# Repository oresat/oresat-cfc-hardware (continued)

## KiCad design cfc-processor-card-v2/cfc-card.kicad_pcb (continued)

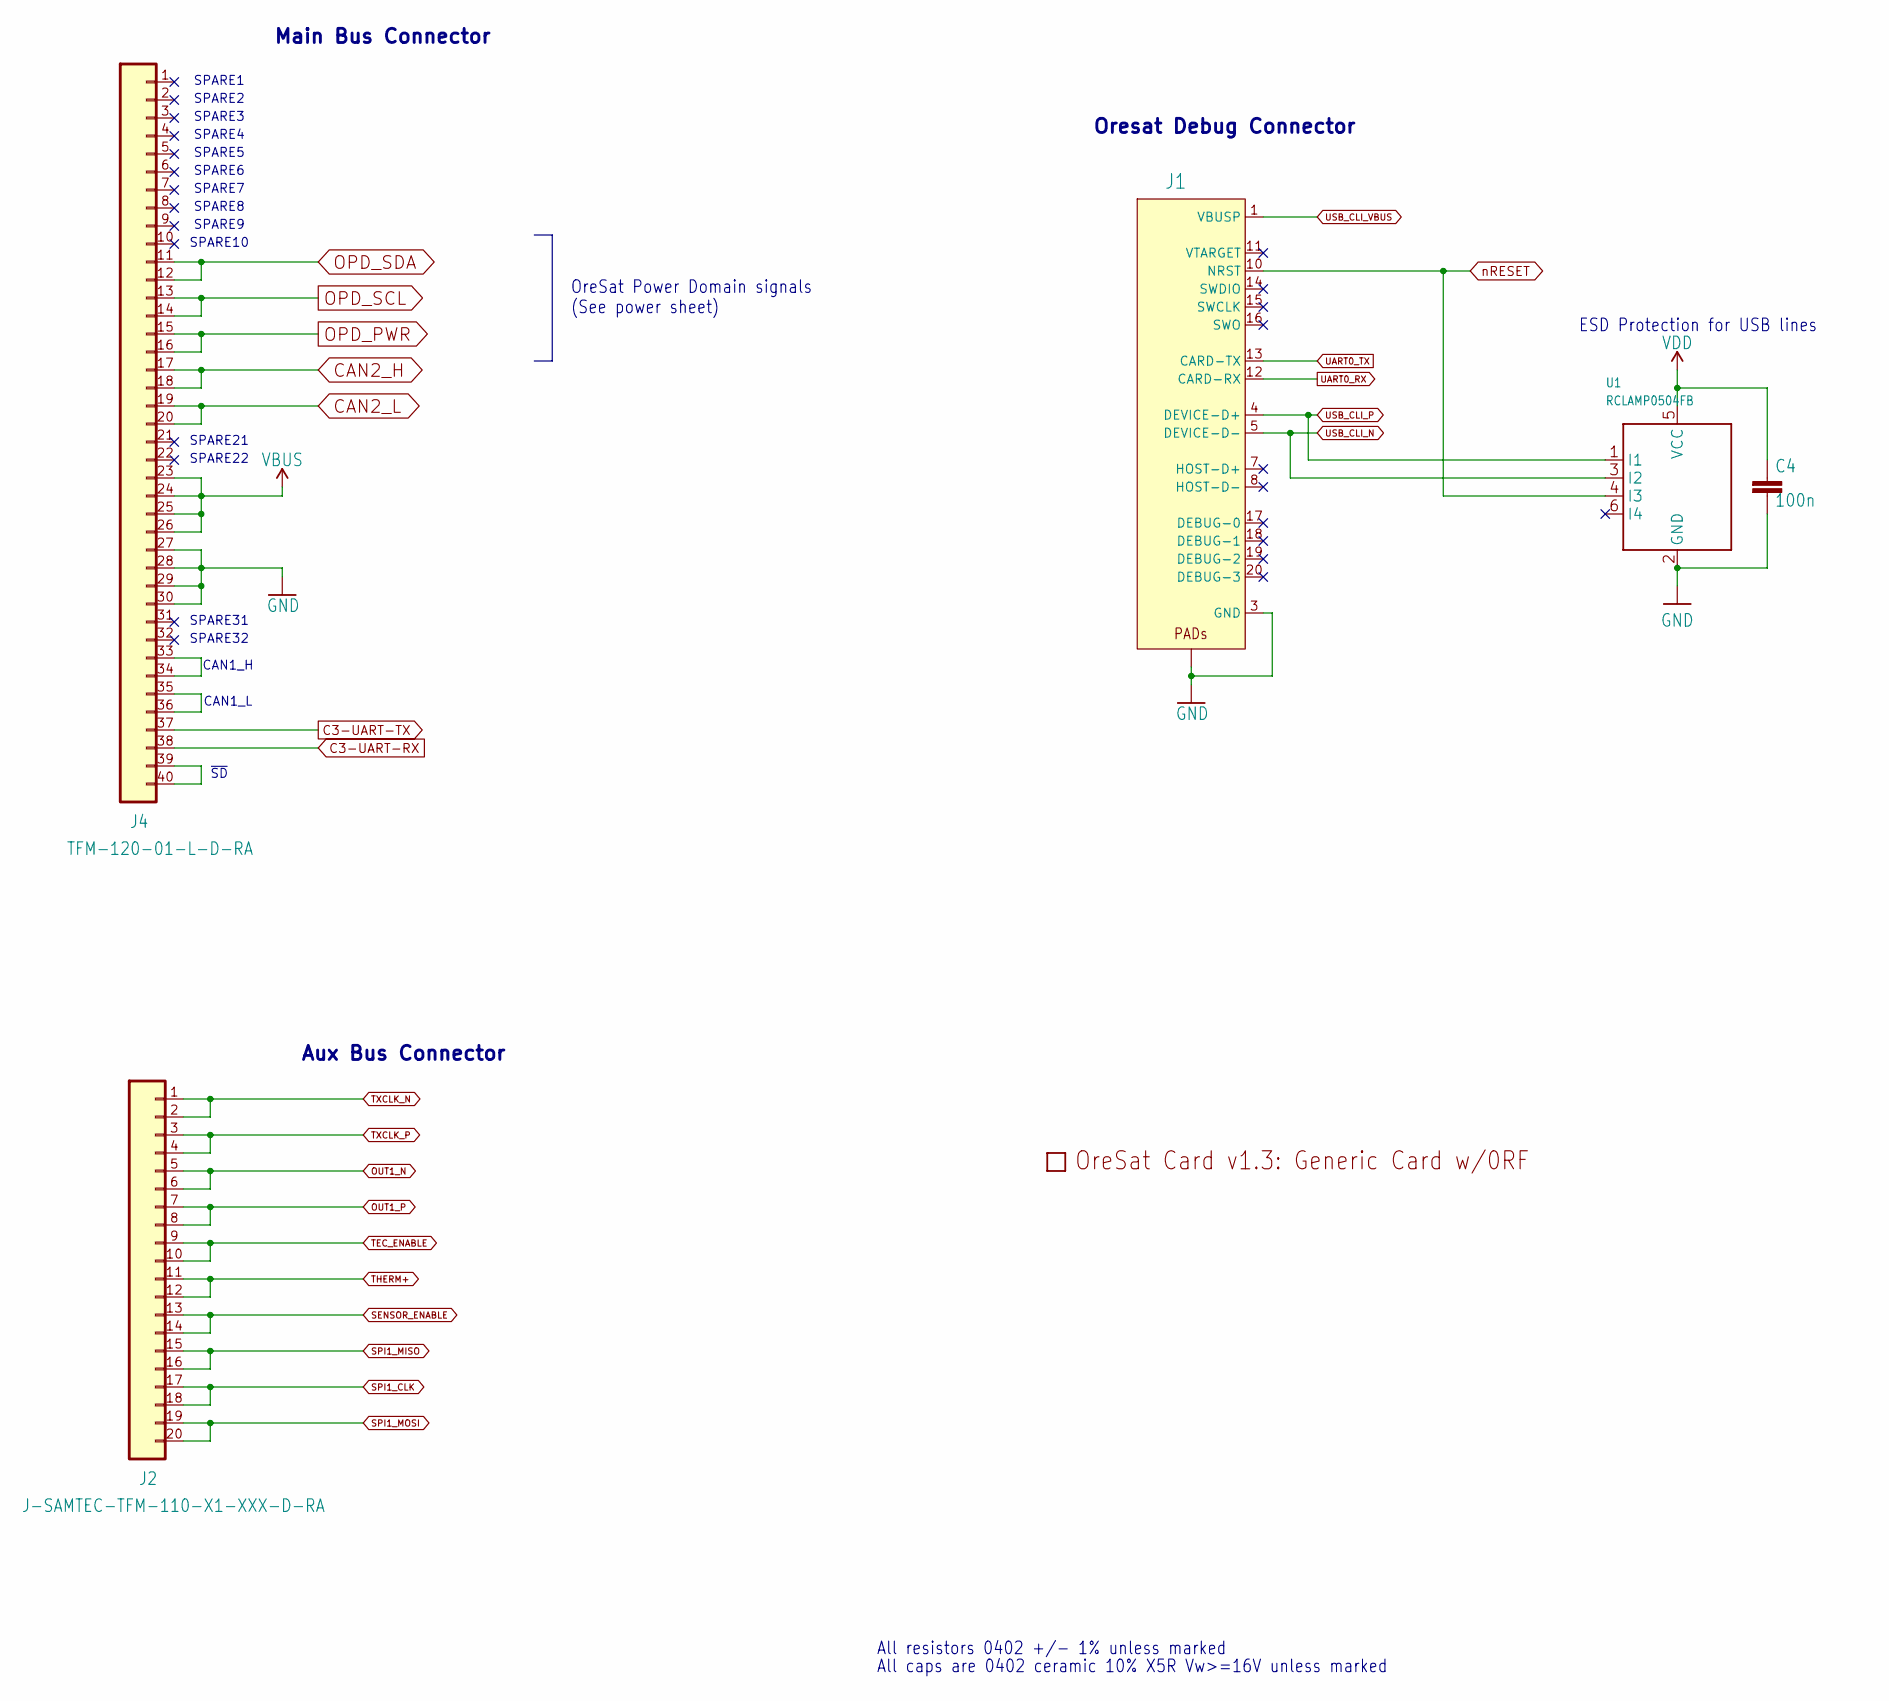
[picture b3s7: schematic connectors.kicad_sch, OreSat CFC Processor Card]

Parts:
C4: 100n; 0603-C-NOSILK; MPN TMK107BJ104KAHT
J1: 2-1734592-0; J-TE-2-1734592-0; MPN 2-1734592-0
J2: J-SAMTEC-TFM-110-X1-XXX-D-RA; MPN TFM-110-01-L-D-RA
J4: TFM-120-01-L-D-RA; J-SAMTEC-TFM-120-X1-XXX-D-RA; MPN TFM-120-01-L-D-RA
PCB1: ORESAT-CARD-V1.3-GENERIC-0RF; MPN N/A
U1: RCLAMP0504FB; SC70-6; MPN RCLAMP0504FBTCT

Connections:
C3-UART-RX: J4.38; also elsewhere on the board
C3-UART-TX: J4.37; also elsewhere on the board
CAN2_H: J4.17, J4.18; also elsewhere on the board
CAN2_L: J4.19, J4.20; also elsewhere on the board
GND: C4.2, J1.3 (GND), J1.6 (GND), J1.9 (GND), J1.PAD1 (PAD), J1.PAD2 (PAD), J4.27, J4.28, J4.29, J4.30, U1.2 (GND); also elsewhere on the board
unnamed: J4.33, J4.34
unnamed: J4.35, J4.36
unnamed: J4.39, J4.40
OPD_PWR: J4.15, J4.16; also elsewhere on the board
OPD_SCL: J4.13, J4.14; also elsewhere on the board
OPD_SDA: J4.11, J4.12; also elsewhere on the board
OUT1_N: J2.5, J2.6; also elsewhere on the board
OUT1_P: J2.7, J2.8; also elsewhere on the board
SENSOR_ENABLE: J2.13, J2.14; also elsewhere on the board
SPI1_CLK: J2.17, J2.18; also elsewhere on the board
SPI1_MISO: J2.15, J2.16; also elsewhere on the board
SPI1_MOSI: J2.19, J2.20; also elsewhere on the board
TEC_ENABLE: J2.9, J2.10; also elsewhere on the board
THERM+: J2.11, J2.12; also elsewhere on the board
TXCLK_N: J2.1, J2.2; also elsewhere on the board
TXCLK_P: J2.3, J2.4; also elsewhere on the board
UART0_RX: J1.12 (CARD-RX); also elsewhere on the board
UART0_TX: J1.13 (CARD-TX); also elsewhere on the board
USB_CLI_N: J1.5 (DEVICE-D-), U1.3 (I2); also elsewhere on the board
USB_CLI_P: J1.4 (DEVICE-D+), U1.1 (I1); also elsewhere on the board
USB_CLI_VBUS: J1.1 (VBUSP), J1.2 (VBUSP); also elsewhere on the board
VBUS: J4.23, J4.24, J4.25, J4.26; also elsewhere on the board
VDD: C4.1, U1.5 (VCC); also elsewhere on the board
nRESET: J1.10 (NRST), U1.4 (I3); also elsewhere on the board

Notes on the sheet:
SPARE31
Oresat Debug Connector
All caps are 0402 ceramic 10% X5R Vw>=16V unless marked
SPARE10
ESD Protection for USB lines
~{SD}
All resistors 0402 +/- 1% unless marked
SPARE8
CAN1_L
SPARE3
SPARE32
SPARE5
SPARE2
SPARE22
OreSat Power Domain signals (See power sheet)
Main Bus Connector
SPARE21
SPARE6
CAN1_H
SPARE7
Aux Bus Connector
SPARE4
SPARE9
SPARE1

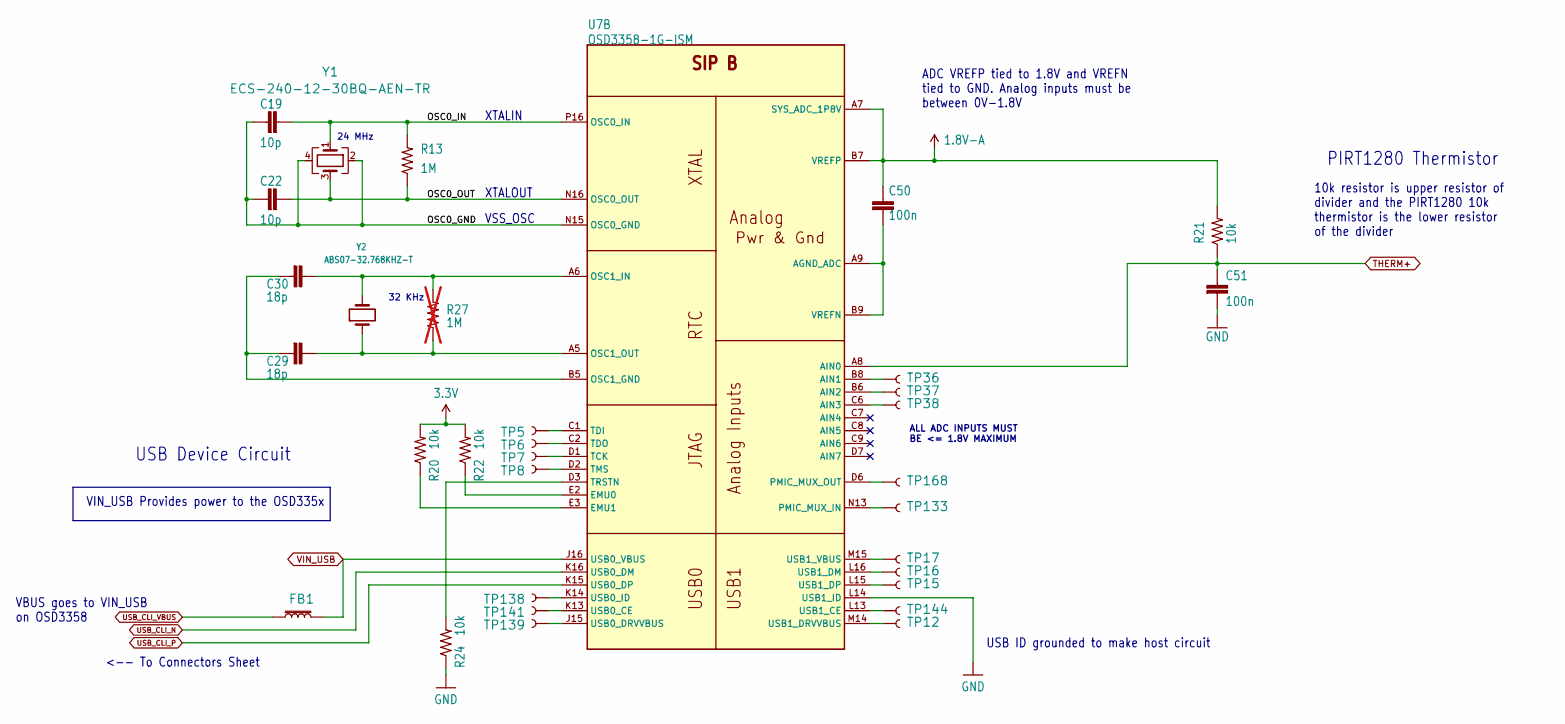
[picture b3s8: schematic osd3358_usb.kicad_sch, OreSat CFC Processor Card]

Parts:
C19, C22: 10p; 0603-C-NOSILK; MPN C0603C100J5GACAUTO
C29, C30: 18p; 0603-C-NOSILK; MPN C0603C180F5GACAUTO
C50, C51: 100n; 0603-C-NOSILK; MPN TMK107BJ104KAHT
FB1: BLM18KG300JH1D; L_0603_1608Metric; MPN BLM18KG300JH1D
R13: 1M; 0603-C-NOSILK; MPN RMCF0603FG1M00
R20, R21, R22, R24: 10k; 0603-C-NOSILK; MPN RMCF0603FT10K0
R27: 1M; 0603-C-NOSILK; not fitted
TP5, TP6, TP7, TP8, TP12, TP15, TP16, TP17, TP36, TP37, TP38, TP133, TP138, TP139, TP141, TP144, TP168: TEST-POINT3X4; PAD.03X.04
U7: OSD3358-1G-ISM; U-Octavo-OSD335X-BGA-256; MPN OSD3358-1G-ISM
Y1: ECS-240-12-30BQ-AEN-TR; CRYSTAL-5X3.2-4SMD; MPN ECS-240-12-30BQ-AEN-TR
Y2: ABS07-32.768KHZ-T; CRYSTAL_3.2X1.5; MPN ABS07-32.768KHZ-T

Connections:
1.8V-A: C50.1, R21.2, U7.A7 (SYS_ADC_1P8V), U7.B7 (VREFP)
3.3V: R20.2, R22.2; also elsewhere on the board
/OSD3358: SIP B (USB, XTAL, ADC)/OSC0_GND: C19.1, C22.1, U7.N15 (OSC0_GND), Y1.2, Y1.4
/OSD3358: SIP B (USB, XTAL, ADC)/OSC0_IN: C19.2, R13.2, U7.P16 (OSC0_IN), Y1.1
/OSD3358: SIP B (USB, XTAL, ADC)/OSC0_OUT: C22.2, R13.1, U7.N16 (OSC0_OUT), Y1.3
GND: C51.2, R24.1, U7.L14 (USB1_ID); also elsewhere on the board
unnamed: TP5.P$1 (1), U7.C1 (TDI)
unnamed: TP6.P$1 (1), U7.C2 (TDO)
unnamed: TP7.P$1 (1), U7.D1 (TCK)
unnamed: TP8.P$1 (1), U7.D2 (TMS)
unnamed: TP12.P$1 (1), U7.M14 (USB1_DRVVBUS)
unnamed: TP15.P$1 (1), U7.L15 (USB1_DP)
unnamed: TP16.P$1 (1), U7.L16 (USB1_DM)
unnamed: TP17.P$1 (1), U7.M15 (USB1_VBUS)
unnamed: TP36.P$1 (1), U7.B8 (AIN1)
unnamed: TP37.P$1 (1), U7.B6 (AIN2)
unnamed: TP38.P$1 (1), U7.C6 (AIN3)
unnamed: TP133.P$1 (1), U7.N13 (PMIC_MUX_IN)
unnamed: TP138.P$1 (1), U7.K14 (USB0_ID)
unnamed: TP139.P$1 (1), U7.J15 (USB0_DRVVBUS)
unnamed: TP141.P$1 (1), U7.K13 (USB0_CE)
unnamed: TP144.P$1 (1), U7.L13 (USB1_CE)
unnamed: TP168.P$1 (1), U7.D6 (PMIC_MUX_OUT)
unnamed: C50.2, U7.A9 (AGND_ADC), U7.B9 (VREFN)
unnamed: R22.1, U7.E2 (EMU0)
unnamed: R20.1, U7.E3 (EMU1)
unnamed: C29.2, C30.2, U7.B5 (OSC1_GND)
unnamed: C30.1, R27.2, U7.A6 (OSC1_IN), Y2.2
unnamed: C29.1, R27.1, U7.A5 (OSC1_OUT), Y2.1
unnamed: R24.2, U7.D3 (TRSTN)
THERM+: C51.1, R21.1, U7.A8 (AIN0); also elsewhere on the board
USB_CLI_N: U7.K16 (USB0_DM); also elsewhere on the board
USB_CLI_P: U7.K15 (USB0_DP); also elsewhere on the board
USB_CLI_VBUS: FB1.1; also elsewhere on the board
VIN_USB: FB1.2, U7.J16 (USB0_VBUS); also elsewhere on the board

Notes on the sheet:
XTALOUT
<-- To Connectors Sheet
USB ID grounded to make host circuit
VSS_OSC
ADC VREFP tied to 1.8V and VREFN tied to GND. Analog inputs must be between 0V-1.8V
PIRT1280 Thermistor
VBUS goes to VIN_USB on OSD3358
USB Device Circuit
VIN_USB Provides power to the OSD335x
24 MHz
10k resistor is upper resistor of divider and the PIRT1280 10k thermistor is the lower resistor of the divider
ALL ADC INPUTS MUST BE <= 1.8V MAXIMUM
32 KHz
XTALIN

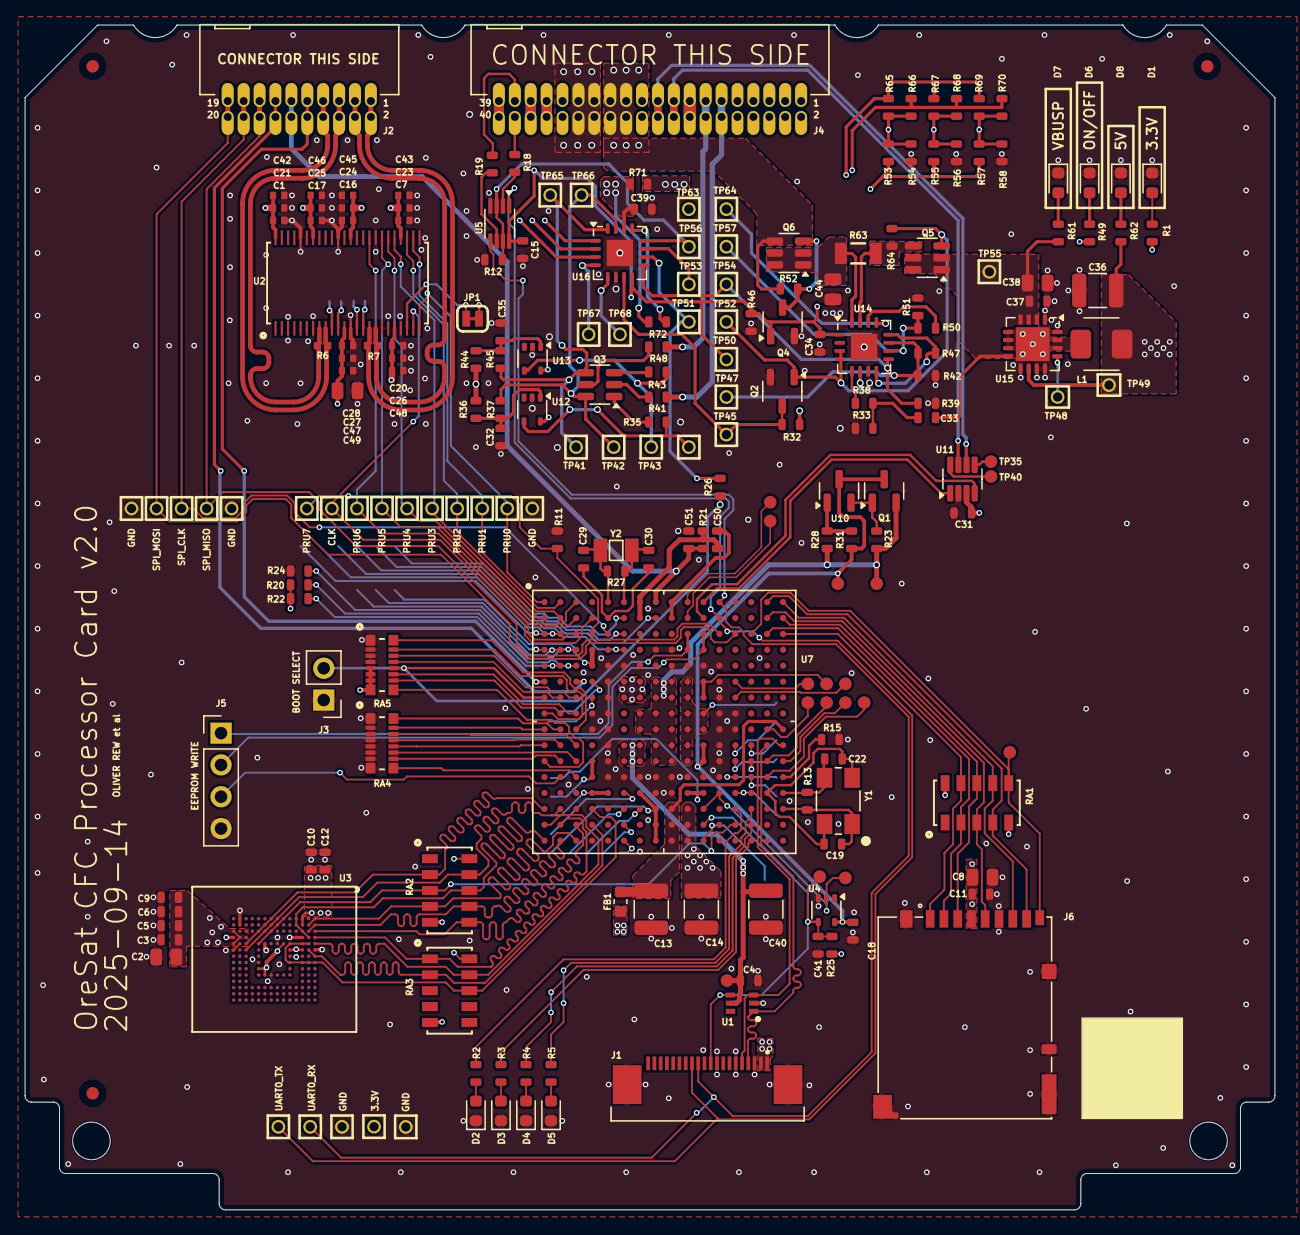
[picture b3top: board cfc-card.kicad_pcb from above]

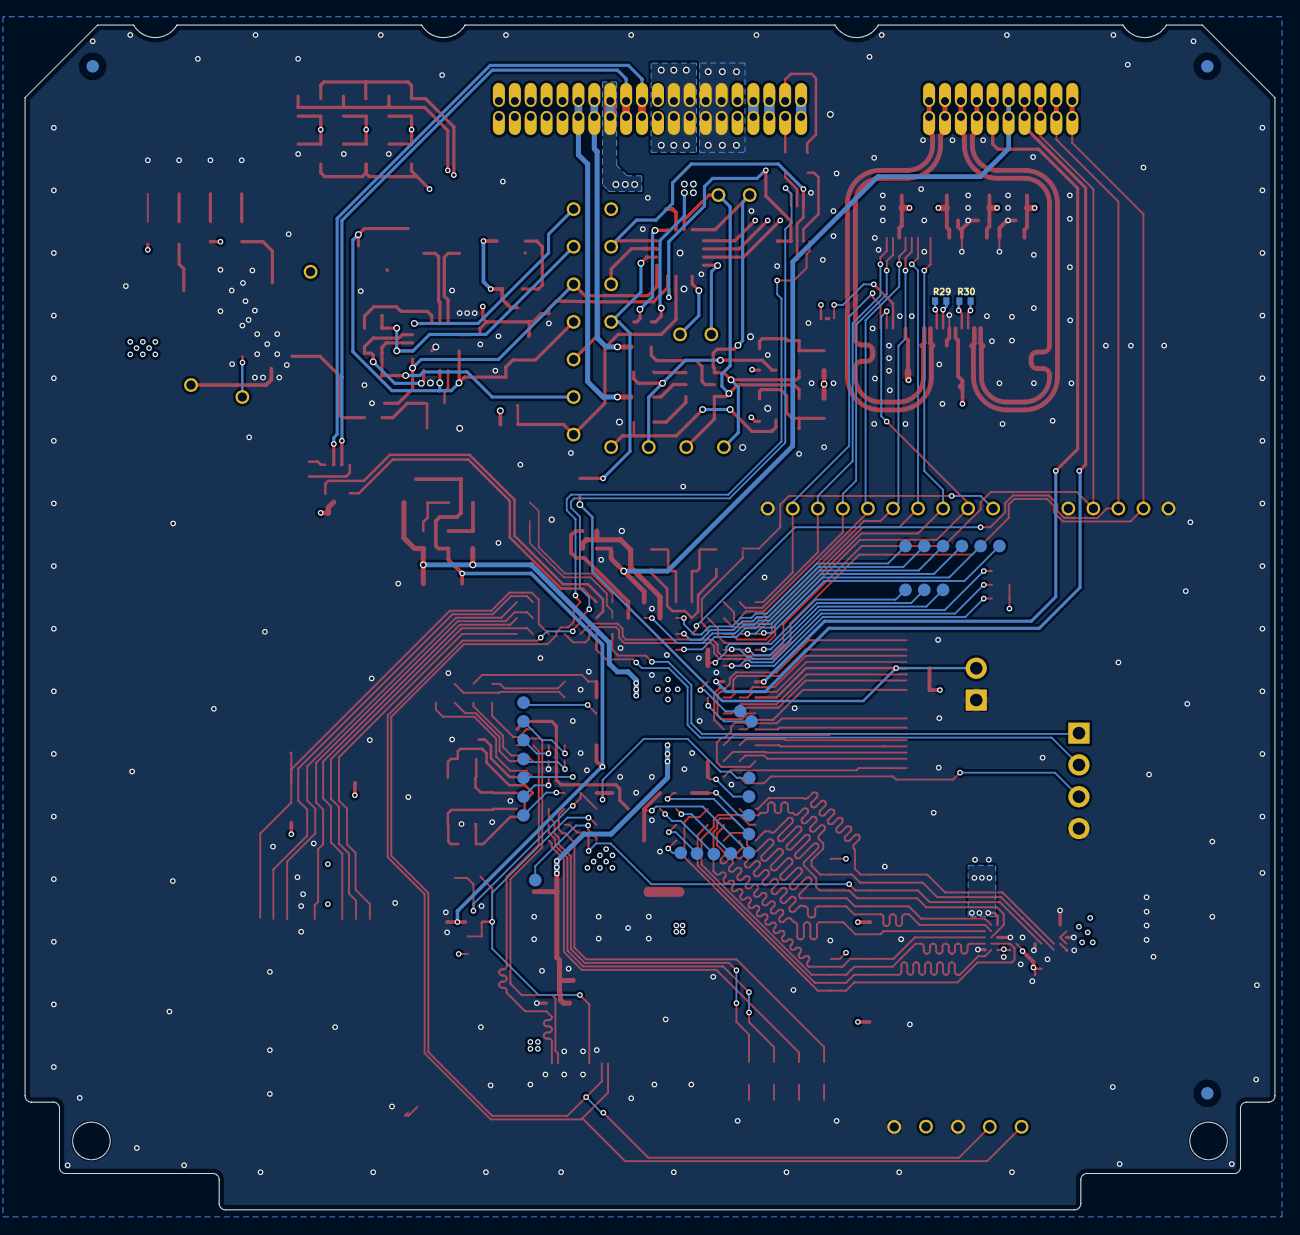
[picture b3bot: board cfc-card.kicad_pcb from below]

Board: 4 copper layers, 99.8 x 94.6 mm, 250 parts (33 on the bottom side), 193 nets.

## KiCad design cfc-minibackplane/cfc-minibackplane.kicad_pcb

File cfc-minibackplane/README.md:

# Oresat CFC Mini-Backplane

This is the backplane for UMBC's Air Harp 2 sensor, which is going to include a PIRT SWIR sensor using OreSat's CFC system.

## Requirements:

* Match the DXF outline from Joe, including placement of connectors and the fastener holes.
   * Probably remove solder mask from both sides of those fastener holes just in case.
   * Probably put the external connectors in the upper right hand corner.
* Use an OreSat 20 pin debug connector on this backplane so we can run USB from the CFC processor to the external connector using the CFC processor's debug connector.
* External connections
   * Power should come through a 0.2 inch euroterminal for two 20 AWG wires.
   * USB should be via a [Harwin M80-5400442](https://www.digikey.com/en/products/detail/harwin-inc/M80-5400442/4953167) connector. Pin-out is determined by us.
       * signals: USB D+, USB D-, Vbus, and GND.
       * Vbus should go through a 10k ohm resistor between the 20 pin debug connector and the Harwin connector.
       
## Required changes to the CFC Processor and CFC sensor boards

Easiest thing to do:

* Both OPDs should come on by default, so we need to bypass or hack the OPDs to turn on.
* We may want to figure out some way to power the local OPDs so they're not doing anything weird with their connections to the Octavo.

A Ben Idea:

* Add a 8.4V to 5V LDO, a Trinket M0, two 4.7K resistors, and use Oliver Rew's Arduino code to turn on both CFC cards
* This assumes we have Trinkets, which I believe we have a bunch lying around.
* This is cute because we don't have to modify the sensor or processor card, which I hate doing.
* Be careful of the 8.4V max input voltage can power the trinket without frying it (thus the 5V LDO).

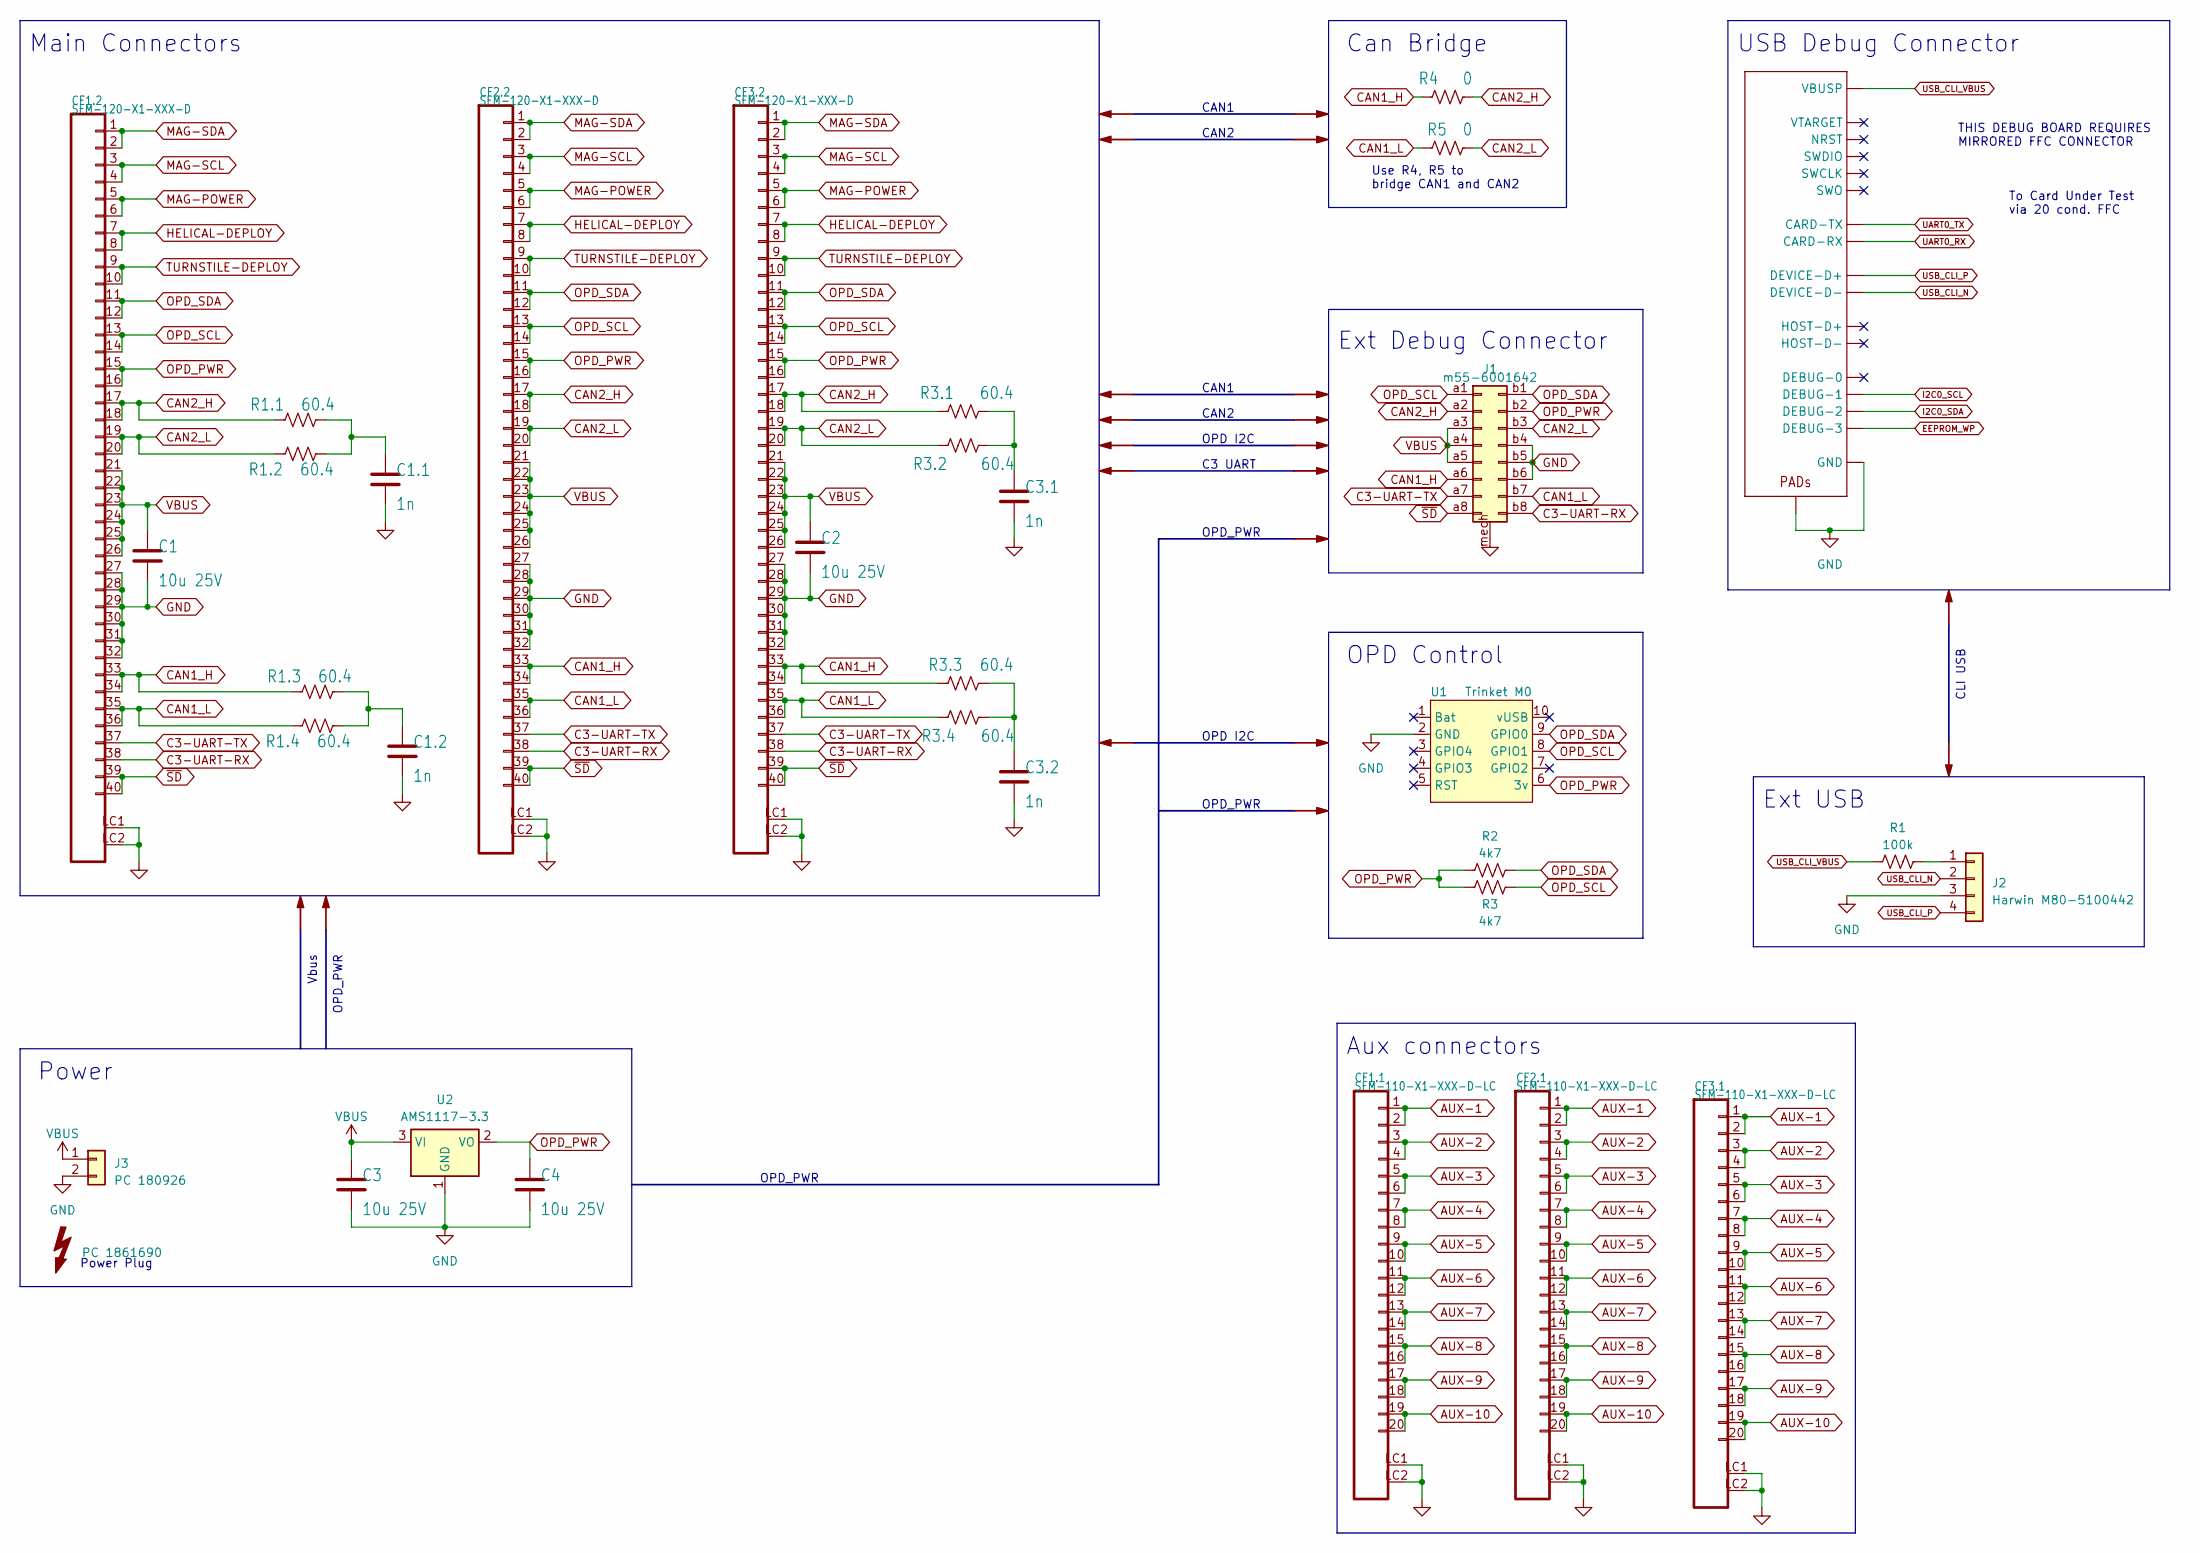
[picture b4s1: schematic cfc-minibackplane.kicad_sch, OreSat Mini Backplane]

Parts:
C1, C2, C3, C4: 10u 25V; C_1206_3216Metric; MPN 490-14533-1-ND
C1.1, C1.2, C3.1, C3.2: 1n; C_0603_1608Metric; MPN GCM1885C2A102JA16D
CF1.1, CF2.1, CF3.1: SFM-110-X1-XXX-D-LC; J-SAMTEC-CF-SFM-110-X1-XXX-D-LC; MPN SFM-110-01-L-D-LC
CF1.2, CF2.2, CF3.2: SFM-120-X1-XXX-D; J-SAMTEC-SFM-120-X1-XXX-D; MPN SFM-120-01-L-D-LC
J1: m55-6001642; MPN 952-3836-1-ND
J2: Harwin M80-5100442; J-Harwin-M80-5100442; MPN M80-5100442
J3: PC 180926; PhoenixContact_MSTBV_2,5_2-GF_1x02_P5.00mm_Vertical_Threade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; MPN 1809267
J3.1: PC 1861690; MPN 1861690
J4: ORESAT-DEBUG-CONNECTOR-ALL; J-TE_2-1734592-0_FFC_MIRRORED; MPN 2-1734592-0
R1: 100k; R_0603_1608Metric; MPN ESR18EZPF1003
R1.1, R1.2, R1.3, R1.4, R3.1, R3.2, R3.3, R3.4: 60.4; R_1206_3216Metric; MPN ESR18EZPF60R4
R2, R3: 4k7; R_0603_1608Metric; MPN RMCF0603FT4K70
R4, R5: 0; R_0603_1608Metric; MPN RMCF0603ZT0R00
U1: Trinket M0; Adafruit-Trinket; MPN 3500
U2: AMS1117-3.3; SOT-223-3_TabPin2; MPN AMS1117-3.3

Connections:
AUX-1: CF1.1.1, CF1.1.2, CF2.1.1, CF2.1.2, CF3.1.1, CF3.1.2
AUX-2: CF1.1.3, CF1.1.4, CF2.1.3, CF2.1.4, CF3.1.3, CF3.1.4
AUX-3: CF1.1.5, CF1.1.6, CF2.1.5, CF2.1.6, CF3.1.5, CF3.1.6
AUX-4: CF1.1.7, CF1.1.8, CF2.1.7, CF2.1.8, CF3.1.7, CF3.1.8
AUX-5: CF1.1.9, CF1.1.10, CF2.1.9, CF2.1.10, CF3.1.9, CF3.1.10
AUX-6: CF1.1.11, CF1.1.12, CF2.1.11, CF2.1.12, CF3.1.11, CF3.1.12
AUX-7: CF1.1.13, CF1.1.14, CF2.1.13, CF2.1.14, CF3.1.13, CF3.1.14
AUX-8: CF1.1.15, CF1.1.16, CF2.1.15, CF2.1.16, CF3.1.15, CF3.1.16
AUX-9: CF1.1.17, CF1.1.18, CF2.1.17, CF2.1.18, CF3.1.17, CF3.1.18
AUX-10: CF1.1.19, CF1.1.20, CF2.1.19, CF2.1.20, CF3.1.19, CF3.1.20
C3-UART-RX: CF1.2.38, CF2.2.38, CF3.2.38, J1.b8
C3-UART-TX: CF1.2.37, CF2.2.37, CF3.2.37, J1.a7
CAN1_H: CF1.2.33, CF1.2.34, CF2.2.33, CF2.2.34, CF3.2.33, CF3.2.34, J1.a6, R1.3.2, R3.3.1, R4.1
CAN1_L: CF1.2.35, CF1.2.36, CF2.2.35, CF2.2.36, CF3.2.35, CF3.2.36, J1.b7, R1.4.1, R3.4.2, R5.1
CAN2_H: CF1.2.17, CF1.2.18, CF2.2.17, CF2.2.18, CF3.2.17, CF3.2.18, J1.a2, R1.1.2, R3.1.1, R4.2
CAN2_L: CF1.2.19, CF1.2.20, CF2.2.19, CF2.2.20, CF3.2.19, CF3.2.20, J1.b3, R1.2.1, R3.2.2, R5.2
EEPROM_WP: J4.20 (DEBUG-3)
GND: C1.2, C1.1.2, C1.2.2, C2.2, C3.2, C3.1.2, C3.2.2, C4.2, CF1.1.LC1, CF1.1.LC2, CF1.2.27, CF1.2.28, CF1.2.29, CF1.2.30, CF1.2.31, CF1.2.32, CF1.2.LC1, CF1.2.LC2, CF2.1.LC1, CF2.1.LC2, CF2.2.27, CF2.2.28, CF2.2.29, CF2.2.30, CF2.2.31, CF2.2.32, CF2.2.LC1, CF2.2.LC2, CF3.1.LC1, CF3.1.LC2, CF3.2.27, CF3.2.28, CF3.2.29, CF3.2.30, CF3.2.31, CF3.2.32, CF3.2.LC1, CF3.2.LC2, J1.b4, J1.b5, J1.b6, J1.mech, J2.3, J3.2, J4.3 (GND), J4.6 (GND), J4.9 (GND), J4.PAD1 (PAD), J4.PAD2 (PAD), U1.2 (GND), U2.1 (GND)
HELICAL-DEPLOY: CF1.2.7, CF1.2.8, CF2.2.7, CF2.2.8, CF3.2.7, CF3.2.8
I2C0_SCL: J4.18 (DEBUG-1)
I2C0_SDA: J4.19 (DEBUG-2)
MAG-POWER: CF1.2.5, CF1.2.6, CF2.2.5, CF2.2.6, CF3.2.5, CF3.2.6
MAG-SCL: CF1.2.3, CF1.2.4, CF2.2.3, CF2.2.4, CF3.2.3, CF3.2.4
MAG-SDA: CF1.2.1, CF1.2.2, CF2.2.1, CF2.2.2, CF3.2.1, CF3.2.2
unnamed: C1.1.1, R1.1.1, R1.2.2
unnamed: C1.2.1, R1.3.1, R1.4.2
unnamed: C3.1.1, R3.1.2, R3.2.1
unnamed: C3.2.1, R3.3.2, R3.4.1
unnamed: J2.1, R1.2
OPD_PWR: C4.1, CF1.2.15, CF1.2.16, CF2.2.15, CF2.2.16, CF3.2.15, CF3.2.16, J1.b2, R2.1, R3.1, U1.6 (3v), U2.2 (VO)
OPD_SCL: CF1.2.13, CF1.2.14, CF2.2.13, CF2.2.14, CF3.2.13, CF3.2.14, J1.a1, R3.2, U1.8 (GPIO1)
OPD_SDA: CF1.2.11, CF1.2.12, CF2.2.11, CF2.2.12, CF3.2.11, CF3.2.12, J1.b1, R2.2, U1.9 (GPIO0)
TURNSTILE-DEPLOY: CF1.2.9, CF1.2.10, CF2.2.9, CF2.2.10, CF3.2.9, CF3.2.10
UART0_RX: J4.12 (CARD-RX)
UART0_TX: J4.13 (CARD-TX)
USB_CLI_N: J2.2, J4.5 (DEVICE-D-)
USB_CLI_P: J2.4, J4.4 (DEVICE-D+)
USB_CLI_VBUS: J4.1 (VBUSP), J4.2 (VBUSP), R1.1
VBUS: C1.1, C2.1, C3.1, CF1.2.21, CF1.2.22, CF1.2.23, CF1.2.24, CF1.2.25, CF1.2.26, CF2.2.21, CF2.2.22, CF2.2.23, CF2.2.24, CF2.2.25, CF2.2.26, CF3.2.21, CF3.2.22, CF3.2.23, CF3.2.24, CF3.2.25, CF3.2.26, J1.a3, J1.a4, J1.a5, J3.1, U2.3 (VI)
~SD: CF1.2.39, CF1.2.40, CF2.2.39, CF2.2.40, CF3.2.39, CF3.2.40, J1.a8

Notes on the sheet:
To Card Under Test via 20 cond. FFC
OPD_PWR
Ext Debug Connector
C3 UART
CAN2
OPD Control
Can Bridge
Use R4, R5 to bridge CAN1 and CAN2
Vbus
Ext USB
CAN1
OPD I2C
USB Debug Connector
CLI USB
THIS DEBUG BOARD REQUIRES MIRRORED FFC CONNECTOR
Power
Main Connectors
Power Plug
Aux connectors

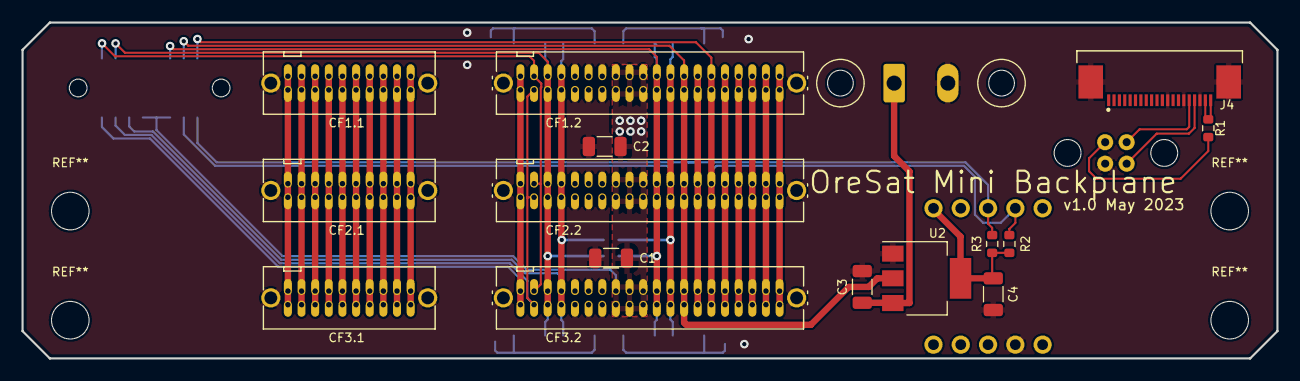
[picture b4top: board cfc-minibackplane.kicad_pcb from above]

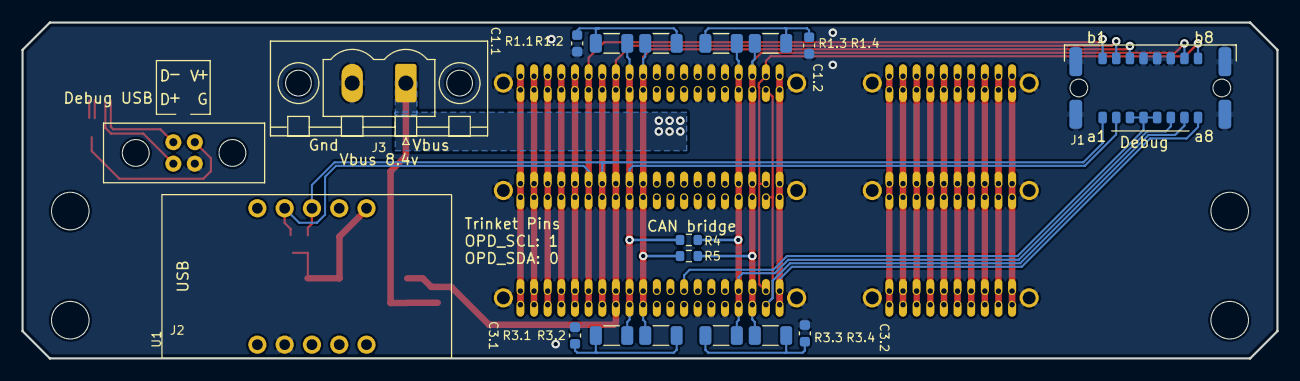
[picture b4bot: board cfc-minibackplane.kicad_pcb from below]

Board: 2 copper layers, 116.8 x 31.3 mm, 33 parts (18 on the bottom side), 35 nets.

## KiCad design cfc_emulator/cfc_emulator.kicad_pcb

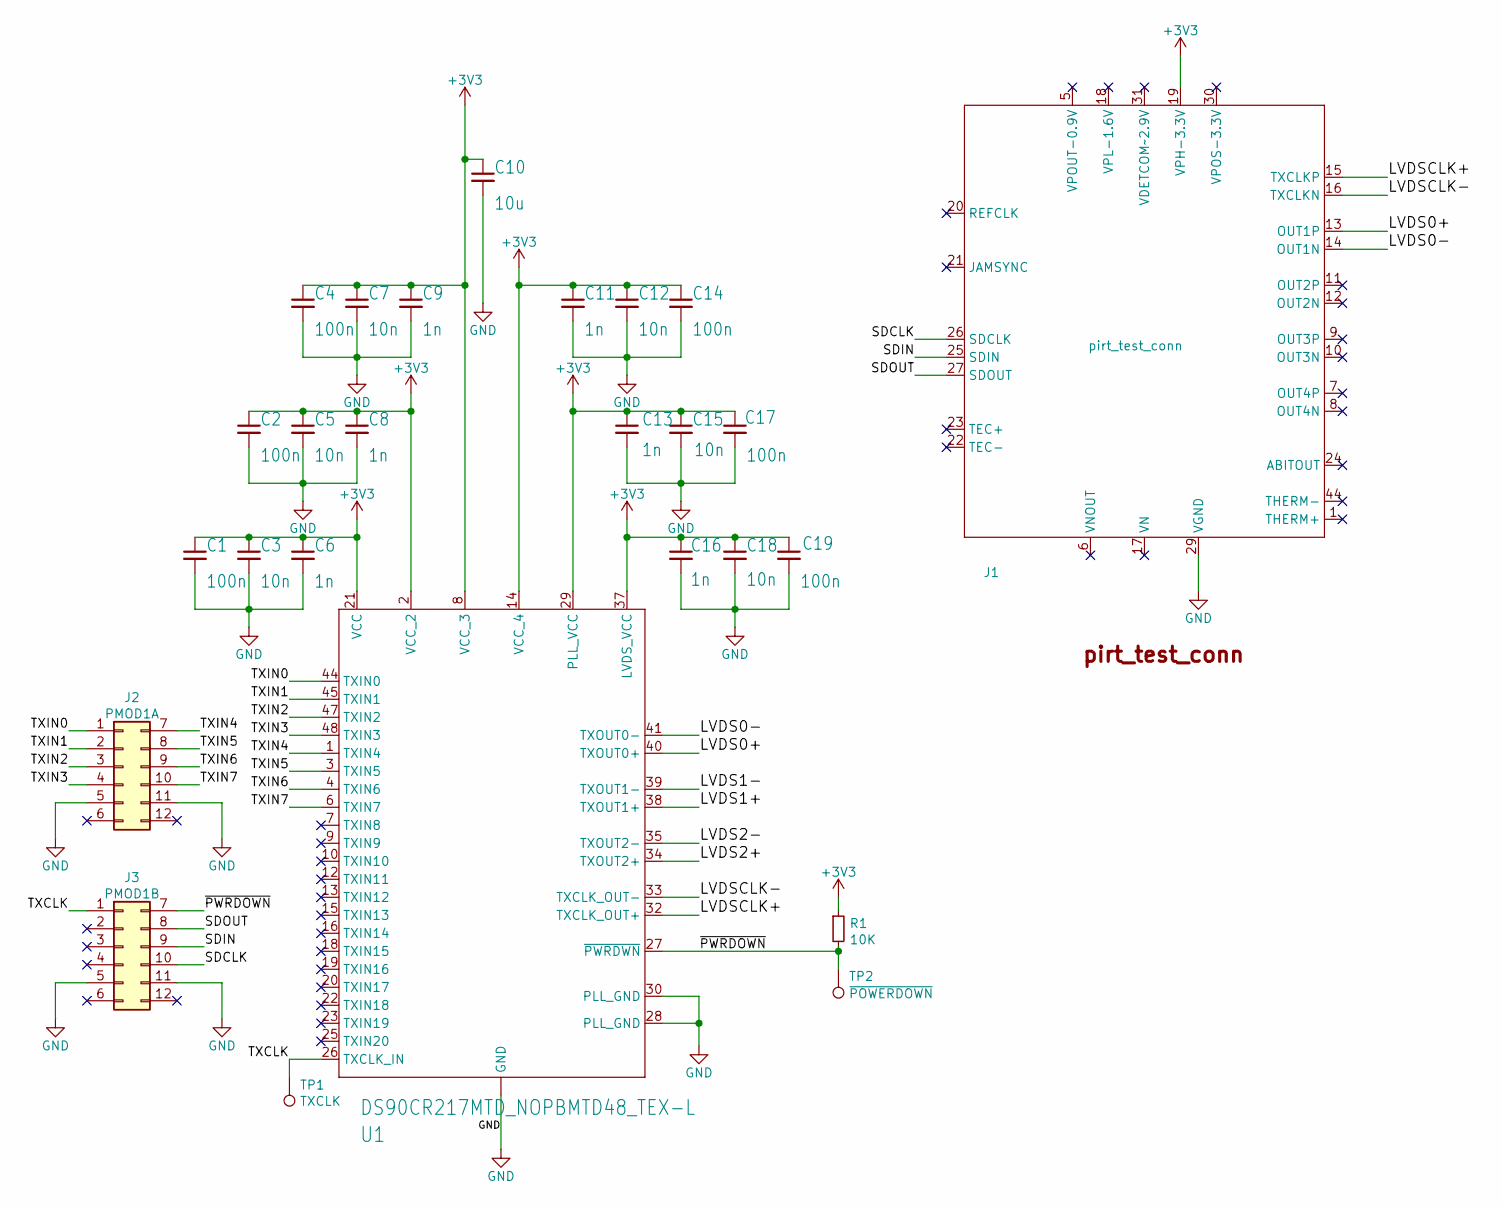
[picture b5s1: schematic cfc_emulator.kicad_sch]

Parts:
C1, C2, C4, C14, C17, C19: C0805C104Z5VACTU; C_0805_2012Metric_Pad1.18x1.45mm_HandSolder
C3, C5, C7, C12, C15, C18: C0603C103M5RACTU; C_0603_1608Metric_Pad1.08x0.95mm_HandSolder
C6, C8, C9, C11, C13, C16: GRM155R71H102KA01J; C_0402_1005Metric_Pad0.74x0.62mm_HandSolder
C10: GRM188R61A106KE69J; C_0603_1608Metric_Pad1.08x0.95mm_HandSolder
J1: pirt_test_conn
J2: PMOD1A; PMOD
J3: PMOD1B; PMOD
R1: 10K; R_0603_1608Metric
TP1: TXCLK; TestPoint_Pad_D2.0mm
TP2: ~POWERDOWN; TestPoint_Pad_D2.0mm
U1: DS90CR217MTD_NOPBMTD48_TEX-L; MTD48

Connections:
+3V3: C1.1, C2.1, C3.1, C4.1, C5.1, C6.1, C7.1, C8.1, C9.1, C10.1, C11.1, C12.1, C13.1, C14.1, C15.1, C16.1, C17.1, C18.1, C19.1, J1.19 (VPH-3.3V), R1.1, U1.2 (VCC_2), U1.8 (VCC_3), U1.14 (VCC_4), U1.21 (VCC), U1.29 (PLL_VCC), U1.37 (LVDS_VCC)
/LVDS0+: J1.13 (OUT1P), U1.40 (TXOUT0+)
/LVDS0-: J1.14 (OUT1N), U1.41 (TXOUT0-)
/LVDS1+: U1.38 (TXOUT1+)
/LVDS1-: U1.39 (TXOUT1-)
/LVDS2+: U1.34 (TXOUT2+)
/LVDS2-: U1.35 (TXOUT2-)
/LVDSCLK+: J1.15 (TXCLKP), U1.32 (TXCLK_OUT+)
/LVDSCLK-: J1.16 (TXCLKN), U1.33 (TXCLK_OUT-)
/SDCLK: J1.26 (SDCLK), J3.10
/SDIN: J1.25 (SDIN), J3.9
/SDOUT: J1.27 (SDOUT), J3.8
/TXCLK: J3.1, TP1.1, U1.26 (TXCLK_IN)
/TXIN0: J2.1, U1.44 (TXIN0)
/TXIN1: J2.2, U1.45 (TXIN1)
/TXIN2: J2.3, U1.47 (TXIN2)
/TXIN3: J2.4, U1.48 (TXIN3)
/TXIN4: J2.7, U1.1 (TXIN4)
/TXIN5: J2.8, U1.3 (TXIN5)
/TXIN6: J2.9, U1.4 (TXIN6)
/TXIN7: J2.10, U1.6 (TXIN7)
/~PWRDOWN: J3.7, R1.2, TP2.1, U1.27 (~PWRDWN)
GND: C1.2, C2.2, C3.2, C4.2, C5.2, C6.2, C7.2, C8.2, C9.2, C10.2, C11.2, C12.2, C13.2, C14.2, C15.2, C16.2, C17.2, C18.2, C19.2, J1.29 (VGND), J2.5, J2.11, J3.5, J3.11, U1.11 (GND), U1.28 (PLL_GND), U1.30 (PLL_GND)

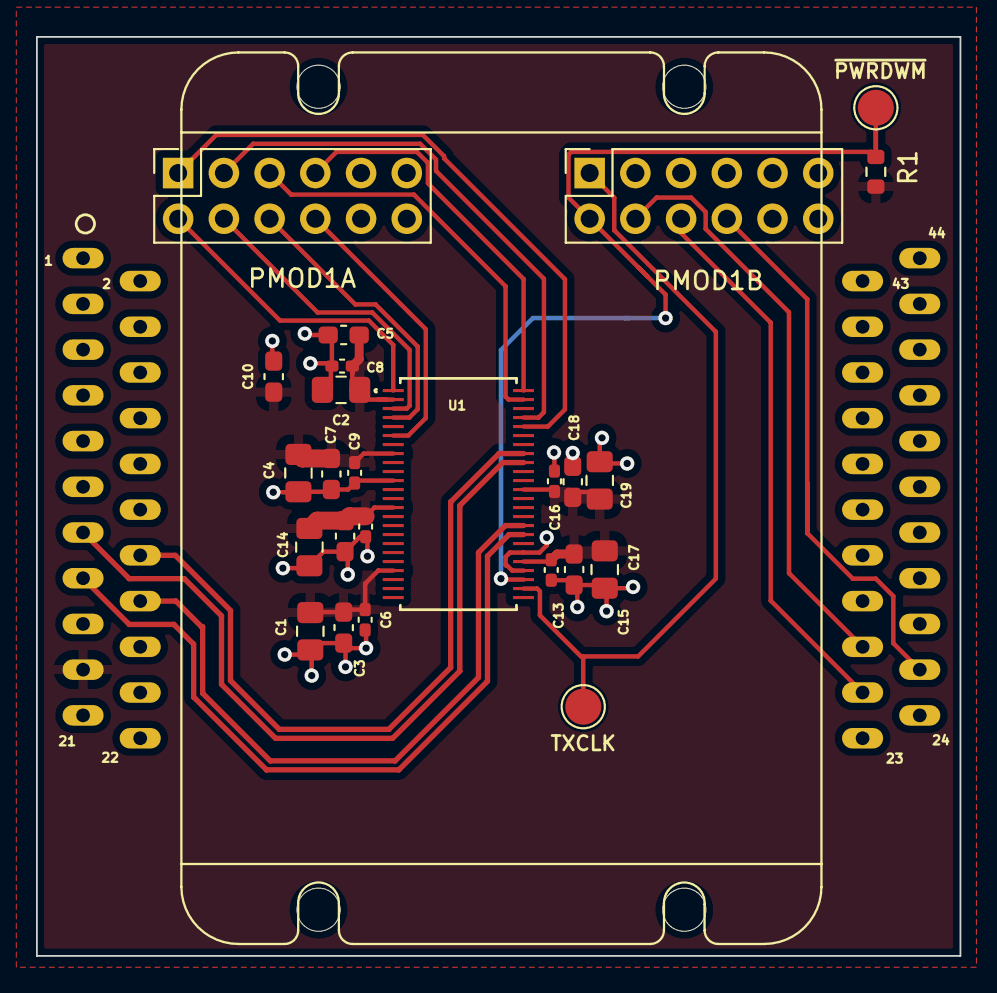
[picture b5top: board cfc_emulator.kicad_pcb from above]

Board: 2 copper layers, 51.3 x 51.1 mm, 26 parts (0 on the bottom side), 19 nets.
